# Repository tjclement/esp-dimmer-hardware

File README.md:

# $5 ESP8266 WiFi LED Dimmer
Custom hardware designs for a super tiny WiFi LED dimmer module based on the ESP8266, to control your lights from any device. __Doesn't need any arduinos or raspberries to work, just the ESP__. If you like this, please give it a star!

__Update:__ The new module design for RGB (i.e. triple channel) LEDs is done. This new design can handle up to ~8.5A of current per channel! Its parts costs the same as the old design, and if you want only one channel, you could just not solder the 2nd and 3rd channel. This way you can use the beefed up design. :)

# Ordering the board
Choose whether you want a single or triple channel dimmer, and then send all files in [single_channel or triple_channel]/gerber_files/ to your PCB house, and all should be fine and dandy!

You can also order the new triple channel design from DirtyPCBs here: 
http://dirtypcbs.com/store/designer/details/tjclement/1329/5-esp8266-rgb-led-dimmer

# Parts
After having ordered the print board, you're going to want to have these parts for every module (mind you, there's two panelized modules per board ordered!):
<table>
  <tr>
    <td colspan="2"><strong>Single Channel (old version)</strong></td>
    <td colspan="2"><strong>Triple Channel (new version)</strong></td>
  </tr>
  <tr>
    <td>Amount</td>
    <td>Description</td>
    <td>Amount</td>
    <td>Description</td>
  </tr>
  <tr>
    <td>1</td>
    <td>ESP8266, ESP-12(E) format</td>
    <td>1</td>
    <td>ESP8266, ESP-12(E) format</td>
  </tr>
  <tr>
    <td>1</td>
    <td>XM1584 Power converter (set to 3.3v!)</td>
    <td>1</td>
    <td>MP2307 MINI 360 Power converter (3.3v!)</td>
  </tr>
  <tr>
    <td>1</td>
    <td>FDS8896 PowerTrench MOSFET</td>
    <td>3</td>
    <td>FDS8896 PowerTrench MOSFET</td>
  </tr>
  <tr>
    <td>2</td>
    <td>KF350-2P screw terminal blocks</td>
    <td>4</td>
    <td>KF350-2P screw terminal blocks</td>
  </tr>
  <tr>
    <td>4</td>
    <td>10k resistors, 0603 format</td>
    <td>6</td>
    <td>10k resistors, 0603 format</td>
  </tr>
</table>

__Total cost: less than $5!__

I order most of it from China, sites like aliexpress.com will have everything you need.

# Firmware
Because this module is essentially a breakout for the ESP8266, you can use any firmware written for it.
I've written a bunch of cool things to get this module running as I want it to, check it out here: http://github.com/tjclement/esp-dimmer-software.

Just hook up a 12V power supply, connect it and the LED strip to the module, and the ESP will be able to control the LEDs. Awesome!

If you're looking for something else (or write your own firmware), have a look at http://esp8266.com for more resources.

You can use a loader like this one to load firmware onto the ESP: https://github.com/themadinventor/esptool.

# Contributing
You can open the .sch and .brd files in Eagle (V7.2+), and make any modifications you see fit. If you add something cool, please create a pull request so we can bring the awesomeness into the community!

# Credits
Heavily inspired by Quindor's original design over at http://blog.quindorian.org/2014/12/esp8266-wifi-led-dimmer-part-1-of-x.html/. We've been sharing design ideas back and forth ever since. Nice job mate!

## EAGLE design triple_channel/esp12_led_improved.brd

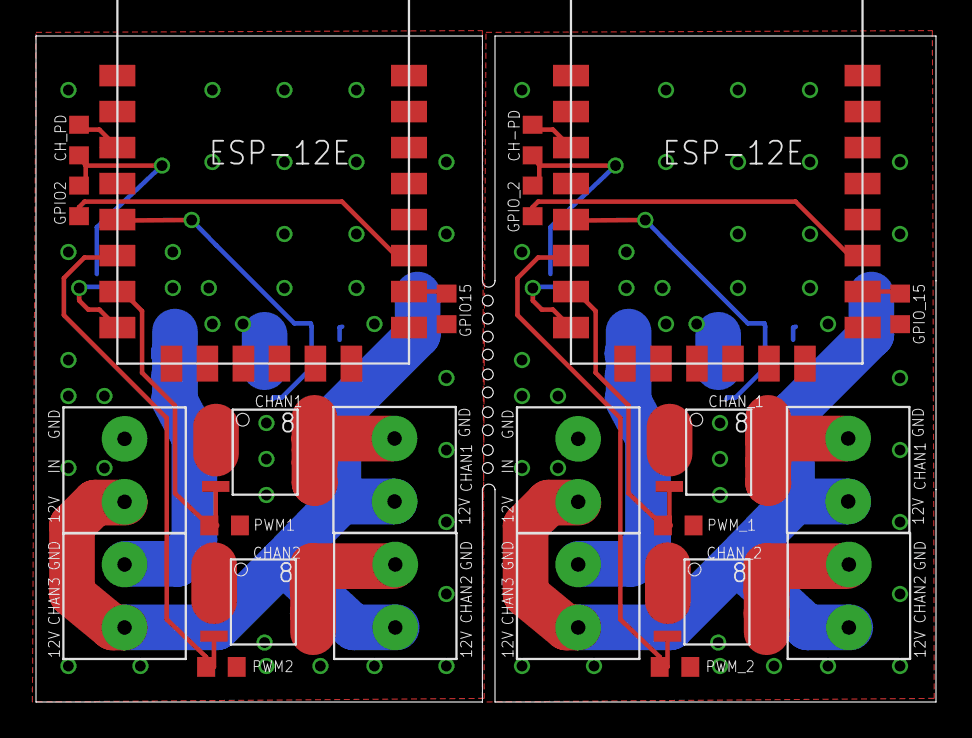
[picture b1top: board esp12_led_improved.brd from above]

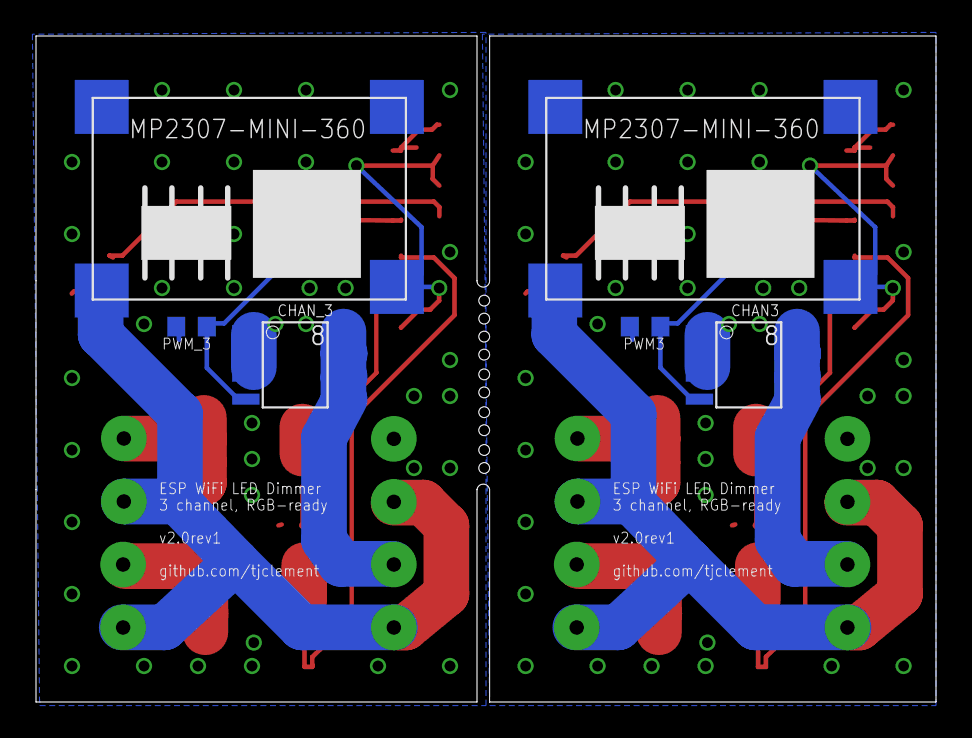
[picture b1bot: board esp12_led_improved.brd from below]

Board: 2 copper layers, 50.0 x 37.0 mm, 30 parts (6 on the bottom side), 26 nets.

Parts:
CH-PD: 10K; R0603
CHAN1, CHAN2, CHAN3: SO-8
CHAN_1, CHAN_2, CHAN_3: SO-8
CH_PD: 10K; R0603
GPIO2, GPIO15: 10K; R0603
GPIO_2, GPIO_15: 10K; R0603
OUT1, OUT2, OUT3, OUT4, OUT5, OUT6: KF350-P2; KF350-2P
PWM1, PWM2, PWM3: 10K; R0603
PWM_1, PWM_2, PWM_3: 10K; R0603
PWR1, PWR2: MP2307-MINI-360
PWR_IN, PWR_IN1: KF350-P2; KF350-2P
XXX, XXX1: ESP8266-ESP12E

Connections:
3.3V: CH_PD.1, GPIO2.1
3.3V1: CH-PD.1, GPIO_2.1
12V: OUT1.1, OUT2.1, OUT3.1, PWR1.12V, PWR_IN.1
12V1: OUT4.1, OUT5.1, OUT6.1, PWR2.12V, PWR_IN1.1
GND: CHAN1.1, CHAN1.2, CHAN1.3, CHAN2.1, CHAN2.2, CHAN2.3, CHAN3.1, CHAN3.2, CHAN3.3, GPIO15.2, PWM1.2, PWM2.2, PWM3.2, PWR1.GND@1, PWR1.GND@2, PWR_IN.2, XXX.9
GND1: CHAN_1.1, CHAN_1.2, CHAN_1.3, CHAN_2.1, CHAN_2.2, CHAN_2.3, CHAN_3.1, CHAN_3.2, CHAN_3.3, GPIO_15.2, PWM_1.2, PWM_2.2, PWM_3.2, PWR2.GND@1, PWR2.GND@2, PWR_IN1.2, XXX1.9
unnamed: CHAN1.5, CHAN1.6, CHAN1.7, CHAN1.8, OUT1.2
unnamed: CH-PD.2, XXX1.3
unnamed: CH_PD.2, XXX.3
unnamed: GPIO2.2, XXX.11
unnamed: CHAN_1.5, CHAN_1.6, CHAN_1.7, CHAN_1.8, OUT4.2
unnamed: CHAN1.4, PWM1.1, XXX.7
unnamed: CHAN2.5, CHAN2.6, CHAN2.7, CHAN2.8, OUT2.2
unnamed: GPIO_2.2, XXX1.11
unnamed: CHAN3.5, CHAN3.6, CHAN3.7, CHAN3.8, OUT3.2
unnamed: CHAN_1.4, PWM_1.1, XXX1.7
unnamed: CHAN2.4, PWM2.1, XXX.6
unnamed: CHAN3.4, PWM3.1, XXX.5
unnamed: CHAN_2.5, CHAN_2.6, CHAN_2.7, CHAN_2.8, OUT5.2
unnamed: CHAN_3.5, CHAN_3.6, CHAN_3.7, CHAN_3.8, OUT6.2
unnamed: CHAN_2.4, PWM_2.1, XXX1.6
unnamed: CHAN_3.4, PWM_3.1, XXX1.5
S$1: PWR1.3.3V, XXX.8
S$2: GPIO15.1, XXX.10
S$3: PWR2.3.3V, XXX1.8
S$4: GPIO_15.1, XXX1.10

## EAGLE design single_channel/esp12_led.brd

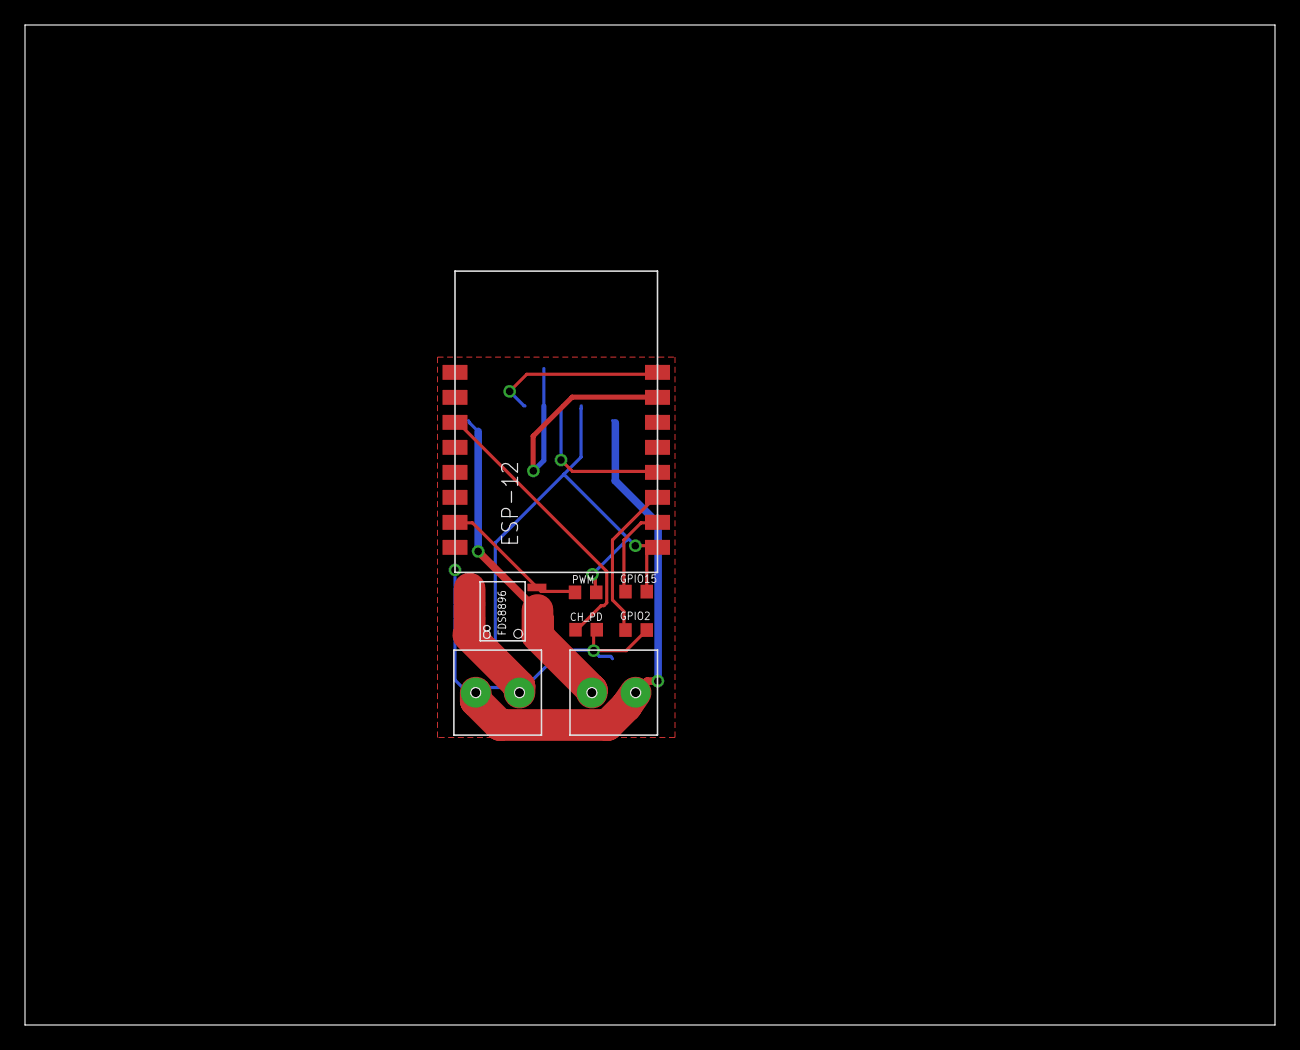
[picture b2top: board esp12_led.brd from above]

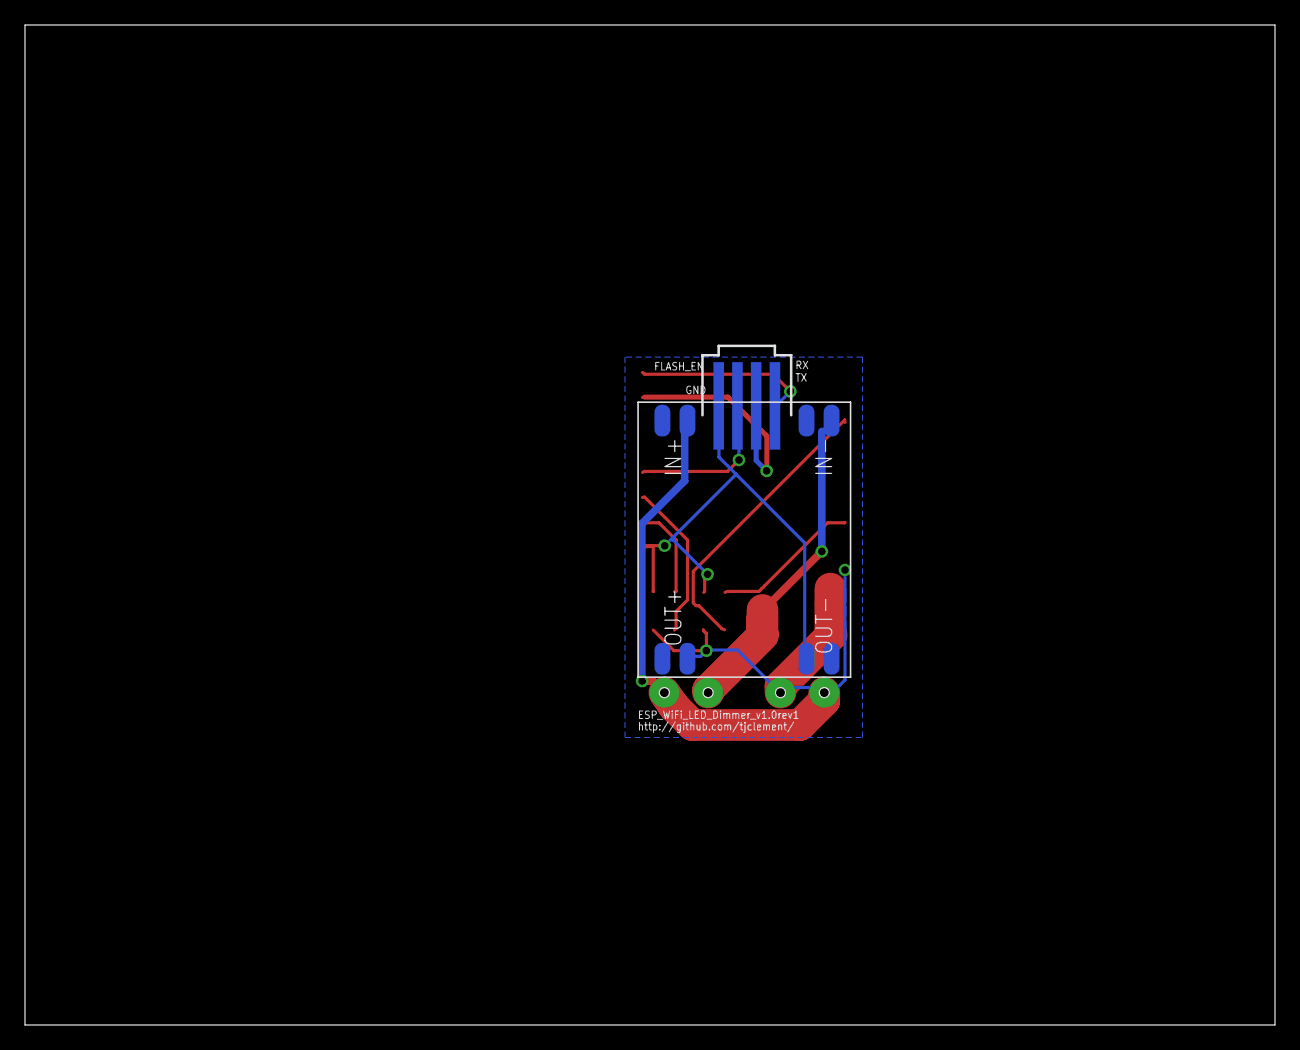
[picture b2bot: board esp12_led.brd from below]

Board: 2 copper layers, 100.0 x 80.0 mm, 10 parts (2 on the bottom side), 13 nets.

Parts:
12V_IN: KF350-P2; KF350-2P
CH_PD: 10k; R0603
DC_CONVERTER: CN1594THROUGH-HOLE; CN1594
ESP-12: ESP8266_ESP-12; ESP8266-ESP12
FDS8896: SO-8
GPIO2, GPIO15: 10k; R0603
LED: KF350-P2; KF350-2P
PROG: 87438-04
PWM: 10k; R0603

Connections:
unnamed: CH_PD.2, DC_CONVERTER.OUT+(1), ESP-12.16, GPIO2.2
unnamed: CH_PD.1, ESP-12.11
unnamed: ESP-12.3, GPIO2.1
unnamed: FDS8896.5, FDS8896.6, FDS8896.7, FDS8896.8, LED.2
unnamed: ESP-12.8, PROG.1
unnamed: DC_CONVERTER.OUT-(2), ESP-12.1, GPIO15.2, PROG.4, PWM.2
unnamed: ESP-12.2, GPIO15.1
unnamed: ESP-12.7, PROG.2
unnamed: ESP-12.4, PROG.3
unnamed: DC_CONVERTER.IN-(1), FDS8896.3
unnamed: 12V_IN.2, DC_CONVERTER.IN+(1), LED.1
S$2: ESP-12.15, FDS8896.4, PWM.1
S$3: 12V_IN.1, FDS8896.1, FDS8896.2

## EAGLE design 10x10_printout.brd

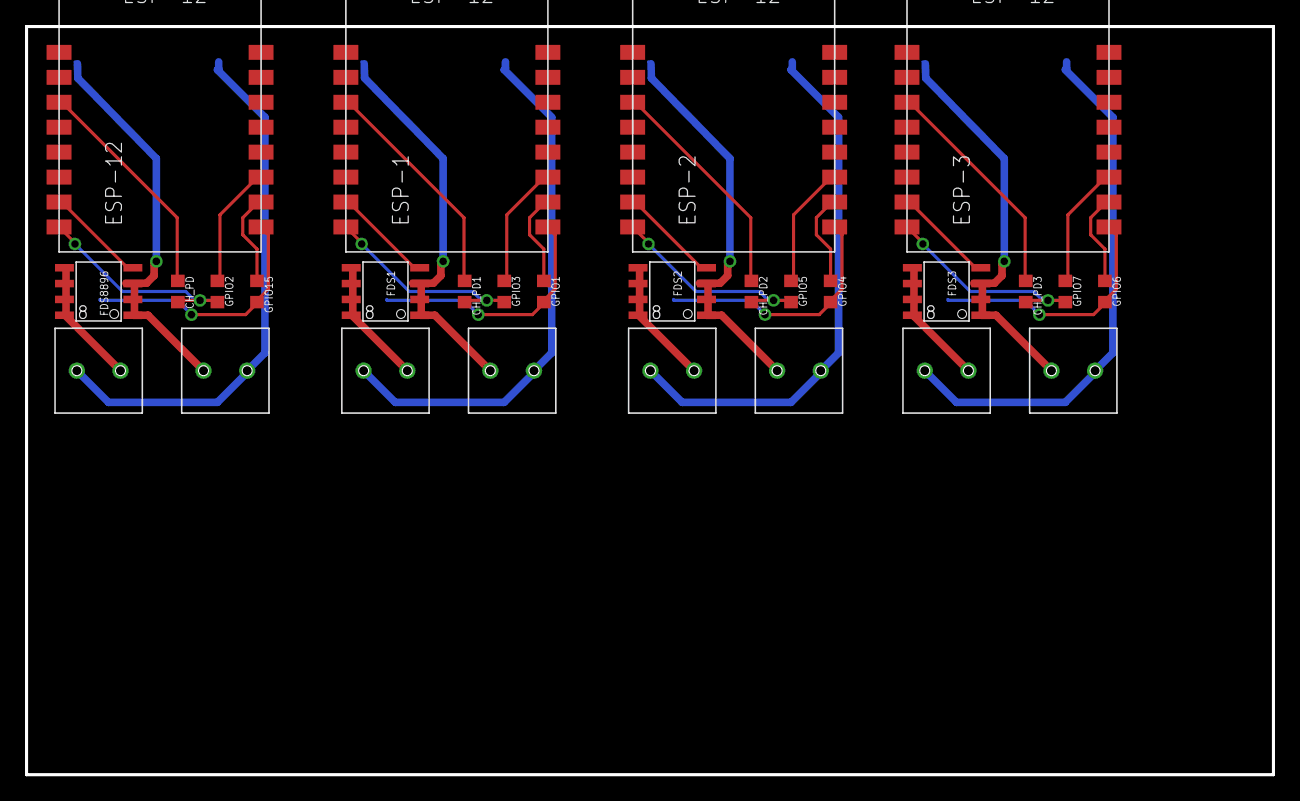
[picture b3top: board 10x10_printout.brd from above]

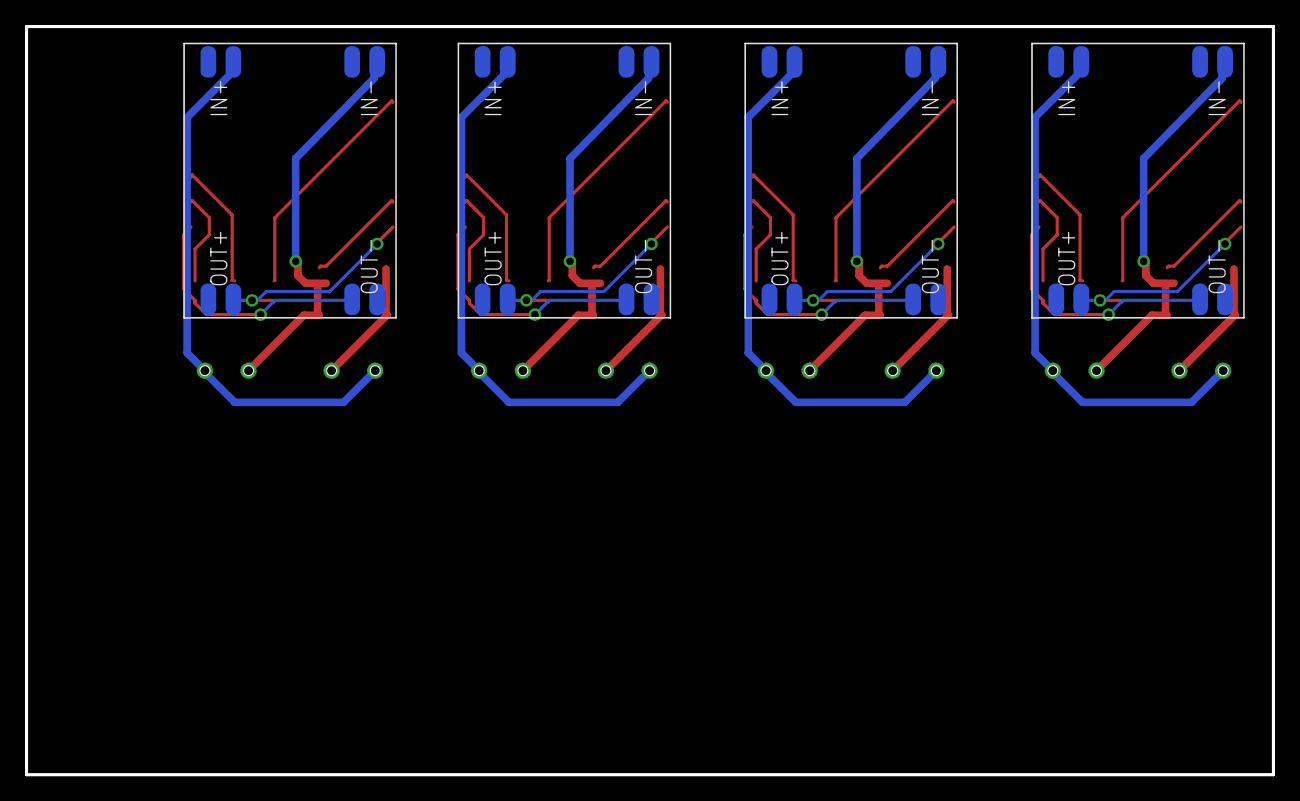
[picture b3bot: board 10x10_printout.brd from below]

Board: 2 copper layers, 100.0 x 60.0 mm, 32 parts (4 on the bottom side), 36 nets.

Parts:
12V_IN, 12V_IN1, 12V_IN2, 12V_IN3: KF350-P2; KF350-2P
CH_PD, CH_PD1, CH_PD2, CH_PD3: 10k; R0603
ESP-1, ESP-2, ESP-3, ESP-12: ESP8266_ESP-12; ESP8266-ESP12
FDS1, FDS2, FDS3, FDS8896: SO-8
GPIO1, GPIO2, GPIO3, GPIO4, GPIO5, GPIO6, GPIO7, GPIO15: 10k; R0603
LED, LED1, LED2, LED3: KF350-P2; KF350-2P
U$1, U$2, U$3, U$4: CN1594THROUGH-HOLE; CN1594

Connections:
unnamed: CH_PD.2, ESP-12.16, GPIO2.2, U$2.OUT+(1)
unnamed: CH_PD.1, ESP-12.11
unnamed: ESP-12.3, GPIO2.1
unnamed: FDS8896.5, FDS8896.6, FDS8896.7, FDS8896.8, LED.2
unnamed: CH_PD1.2, ESP-1.16, GPIO3.2, U$1.OUT+(1)
unnamed: ESP-12.1, GPIO15.2, U$2.OUT-(2)
unnamed: ESP-12.2, GPIO15.1
unnamed: CH_PD1.1, ESP-1.11
unnamed: ESP-1.3, GPIO3.1
unnamed: 12V_IN.1, FDS8896.1, FDS8896.2, FDS8896.3, U$2.IN-(1)
unnamed: ESP-12.15, FDS8896.4
unnamed: 12V_IN.2, LED.1, U$2.IN+(1)
unnamed: ESP-1.1, GPIO1.2, U$1.OUT-(2)
unnamed: ESP-1.2, GPIO1.1
unnamed: FDS1.5, FDS1.6, FDS1.7, FDS1.8, LED1.2
unnamed: ESP-1.15, FDS1.4
unnamed: 12V_IN1.1, FDS1.1, FDS1.2, FDS1.3, U$1.IN-(1)
unnamed: 12V_IN1.2, LED1.1, U$1.IN+(1)
unnamed: CH_PD2.2, ESP-2.16, GPIO5.2, U$3.OUT+(1)
unnamed: CH_PD2.1, ESP-2.11
unnamed: ESP-2.3, GPIO5.1
unnamed: ESP-2.1, GPIO4.2, U$3.OUT-(2)
unnamed: ESP-2.2, GPIO4.1
unnamed: FDS2.5, FDS2.6, FDS2.7, FDS2.8, LED2.2
unnamed: ESP-2.15, FDS2.4
unnamed: 12V_IN2.1, FDS2.1, FDS2.2, FDS2.3, U$3.IN-(1)
unnamed: 12V_IN2.2, LED2.1, U$3.IN+(1)
unnamed: CH_PD3.2, ESP-3.16, GPIO7.2, U$4.OUT+(1)
unnamed: CH_PD3.1, ESP-3.11
unnamed: ESP-3.3, GPIO7.1
unnamed: ESP-3.1, GPIO6.2, U$4.OUT-(2)
unnamed: ESP-3.2, GPIO6.1
unnamed: FDS3.5, FDS3.6, FDS3.7, FDS3.8, LED3.2
unnamed: ESP-3.15, FDS3.4
unnamed: 12V_IN3.1, FDS3.1, FDS3.2, FDS3.3, U$4.IN-(1)
unnamed: 12V_IN3.2, LED3.1, U$4.IN+(1)

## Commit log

2015-05-06 Initial fill, v1.0rev1
2015-05-06 Updated README with explanation and parts list
2015-05-06 Added image preview of board
2015-05-06 Updated image links
2015-05-16 Added first preview module image, without the terminal blocks
2017-01-02 Improved design: Added triple channel (RGB) support, beefed up to ~8.5A per channel.
2017-01-02 Updated parts table
2017-01-02 Added link to DirtyPCBs
2017-01-02 Rephrased contribution section
2017-01-29 Fixed PWM resistors being applied in series instead of as pulldowns
2017-06-20 Fixed DirtyPCBs link. Closes #6, thanks for letting me know!
